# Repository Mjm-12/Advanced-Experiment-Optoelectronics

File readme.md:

# オシロスコープの使い方
このファイルは筑波大学理工学群、応用理工学類応用物理主専攻3年次の専攻実験(テーマ：オプトエレクトロニクス)用に作成しています。  
作成者は2025年度TAの山本隼大(関口・早田研、前期博士課程1年)です。  

使用するオシロスコープはKEYSIGHTの[**EDUX1052G**](https://www.keysight.com/jp/ja/product/EDUX1052G/oscilloscope-50-mhz-2-analog-channels-waveform-generator.html)です。  
マニュアルは[ここ](https://www.keysight.com/jp/ja/assets/9921-02770/user-manuals/9018-70020.pdf)からダウンロードできます。  
このオシロスコープは基本的な機能である波形の観察に加えて、ファンクションジェネレータ機能（波形を発生させる機能）や、周波数特性の測定を一台で完結することができる優れものです。  

他社製のオシロスコープでも同様の使い方で測定を行うことができるので、是非来年以降の研究でも参考にしていただければと思います。  

## プローブについて
プローブはオシロスコープと被測定物の電気的接続を取るためのものです。一般的には細長い棒状のものを使いますが、被測定物や測定する周波数帯によってはBNCケーブルなどを直接繋ぐこともあります。  

### プローブ倍率
プローブには倍率を切り替えるスイッチが付いています。一般的には1:1と10:1の2つが切り替え可能になっていることが多いですが、**本実験では10:1を基本として測定を行いましょう**。その理由としては、プローブの入力インピーダンスをできるだけ大きくして回路や信号への影響を最小限に留めるためです。  
オシロスコープの入力インピーダンスは1MΩ程度のものが多いですが、プローブを10:1にすることで、入力インピーダンスを10倍の10MΩにすることができます。その分、信号の電圧が1/10になってしまうので、オシロスコープ内部で10倍に増幅して表示することになります。  

#### オシロスコープ側の設定
まず、プローブの倍率を変更したいチャンネルを選択します。ここでは例として**Ch1**を選択します。  

**プローブの倍率の確認方法その1**  

次に画面右側のプローブを選択し、倍率をプローブと同様の値に変更します。  
この操作を怠ると、誤った電圧やゲインが表示されてしまうため、セットアップの一環として必ず確認するようにしましょう。  

**プローブの倍率の確認方法その2**  

### プローブの補正
オシロスコープのセットアップとして重要な設定に、プローブの補正があります。ケーブルやオシロスコープの入力部分には容量成分(コンデンサ成分)が存在するため、これを打ち消さないとプローブ自身がLRCフィルタとなってしまい、正しい測定ができません。  
そこで、直列にコンデンサ成分を追加して、容量成分を打ち消す必要があります。  
[参考資料](https://cc.cqpub.co.jp/system/contents/1246/)  

#### 補正方法
まず、補正したいプローブをオシロスコープ下部にある端子と図のように接続します。  

**プローブの接続方法**  

次に接続されているチャンネル選択ボタンを押して、ボタンが点灯していることを確認します。さらに、右上の`Auto Scale`ボタンを押すと、矩形波（方形波）が表示されるはずです。これで補正の準備完了です。  

**プローブ補正の手順**  

プローブには補正用のトリマーが付いています(図参照)。これを調整することで、直列のコンデンサ容量を調整します。エッジが適切な角度になり、理想的な矩形波が得られるように調整してください。十分に調整できたら問題ありません。  

**最適な形状に調整する**  

## 波形の観察方法
オシロスコープの最も基本的な機能である波形観察の方法について解説します。  

まず、大前提として横軸(x軸)方向が時間軸、縦軸(y軸)方向が電圧軸になります。サイン波を印加すれば $y=\sin{x}$ のグラフが描画されるイメージです。上部に時間や電圧のスケールが書いてありますが、これは1目盛りあたりの値を示しています。  

**時間軸と電圧軸で表される**  

### 軸の調整方法
ここからは実際に波形を見やすいい形に調整していきます。例として、プローブの補正に使う矩形波を使います。まず、補正時と同様に`Auto Scale`ボタンを押しましょう。そうすると、ある程度整った波形が描画されるはずです。  

**表示される波形の一例**  

次に、エッジ部分をもっと詳細に見たいとします。電圧軸を拡大・縮小するときは操作部中央の大きなツマミ(`Vertical`と書かれたツマミ)を調整します。ツマミを押し込むと、粗調整モードと微調整モードが切り替わります。  

電圧オフセット(中心の高さ)を切り替えたいときは下にある▲▼が書かれたツマミを調整します。押し込むことでオフセットがゼロに戻ります。  

時間軸方向の調整は`Horizontal`と書いてあるセクションで行います。左の大きいツマミが拡大縮小、右の小さいツマミが時間オフセットです。  
それぞれ押し込むことで、電圧軸方向のそれと同様の切り替えやオフセットのリセットが行えます。  

**電圧軸、時間軸の調整**  

### トリガーの設定
オシロスコープをマスターするうえで、最も重要な設定が**トリガー**です。トリガーとは時間で変動する電圧を安定的に表示するための機能です。トリガーを適切に設定しないと大きく荒ぶった波形となり、これでは到底測定には役立ちません。測定したい波形を確実に捉えるために必須となる機能であり、多くのモードがありますが、今回は低周波を扱ううえで最も基本的な設定に絞って紹介します。  

まず、トリガーモードはいくつかありますが、とりあえず最も一般的なトリガーである**エッジトリガー**を用いることにします。エッジトリガーにも立ち上がりを検出するものと立ち下がりを検出するものがありますが、一般的には立ち上がりを検出するものを選択するとよいでしょう。操作パネル右端の`Trigger`ボタンを押すとトリガーの設定画面が表示されるので、`Trigger Type`に**Edge**、`Slope`に上向きのダイオードのような図を選択します。  

**トリガーの調整**  

次に、トリガーのソースを設定します。これはトリガーをかける波形を選択するもので、今回は**Ch1**を選択します。内蔵のファンクションジェネレータを測定に使っている場合はWave Genをソースに選択してもよいでしょう。  

最後に、トリガーレベルを調整します。右端の`Trigger`と書かれたツマミを調整することで、オレンジのバーが上下することが確認できます。このオレンジバーの横線をトリガーレベルといい、この電圧を超える波形のみを取り出し、表示することができます。  
正しくトリガーを設定すると、波形が安定して表示されます。  

### 各数値を調べる
表示している波形の電圧や周波数を確認したいタイミングは往々にしてありますが、毎度目盛りを読むのは面倒なものです。そのため、デジタルオシロスコープには周波数や周期、電圧の振幅のピーク値や実効値を表示してくれる機能があります。  
`Meas`ボタンを押すことでサイドバーにMeasurementモードが開きます。そこから`Source`を選択し、`Type`を選択します。セレクトノブを押し込むか、`Add Measurement`を押すことで、下部に固定表示することができます。測定データは最大5個まで追加できます。  

**波形の特性の測定方法**  

**複数のSourceの特性を同時に見ることができる**  

### 波形表示を一時停止する
波形表示を一時停止するには右上の`RUN/STOP`ボタンを押します。すると波形が止まり、ボタンが赤くなると思います。  
再開するにはもう一度`RUN/STOP`ボタンを押せばOKです。  

## 周波数特性分析(FRA)
**FRA**(Frequency Response Analyzer)は装置の周波数応答を調べる装置を指し、この機能が本実験で用いるオシロスコープでは実装されています。アンプ等の周波数特性を分析することで、増幅可能な周波数レンジを定量的に評価することが可能です。理想的な特性としては低周波まで高周波まで真っ直ぐ伸びていることが望ましいです。例えば、あるヘッドホンアンプの周波数特性が人間の可聴域より狭いと、音が籠もって聞こえたり、キンキンして聞こえることがあります。また、低周波だけ強い特性を持つ場合は、ベースやバスドラムなどの低音が強調されて聞こえます。  

### 基本的なセットアップ
まず、`Analyze`→`Features`を開き、FRAを選択します。そうすると、左側にグラフが表示されます。  

**FRAのセットアップ方法①**  

次に、被測定物にプローブを取り付けていきます。Setupを開くと、ディレクションが表示されるので、このように接続していきます。具体的にはGenOutと**Ch1**を入力、Ch2を出力に取り付けます。  

**FRAセットアップ方法②(Setupを押すと表示される画面)**  

FRA Setupの画面に戻り、測定のためのパラメータを調整していきます。`Start Freq`と`Stop Freq`に測定したい周波数の上限/下限を入力します。例として、可聴帯域を測定したいとするならば**10Hz~20kHz程度**が望ましいでしょう。  
`Amplitude`は入力するサイン波の大きさを調整します。クリップ（音割れ）しない範囲で調整しつつ、小さすぎるとノイズの影響が支配的になってしまい、正確な測定ができません。あらかじめどれくらいの大きさの信号ならクリップしないか確認しておきましょう。  
`Output Load`はとりあえず**50Ω**で構いません。`Points`は測定点数を示し、点数が多いほど精密な測定が期待出来ますが、その分測定時間が長くなります。可聴域程度であれば**200~300程度**でも十分だと思います。  

### 結果の見方
`ゲイン(Gain)`が<span style="color:#157EFB;">青線</span>、`位相(Phase)`が<span style="color:red;">赤線</span>で表示されています。x軸は周波数で、ゲインの単位はdBで、 $A\,\mathrm{[dB]}=20\log_{10}\frac{V_{OUT}}{V_{IN}}$ で表される無次元量です。0dBで1倍、3dBで約√2倍、6dBで約2倍、20dBで10倍、40dBで100倍と覚えてください。位相は基準信号からの位相のズレを表していますが、本実験ではあまり重要ではないので無視して構いません。回路の発振可能性を評価するときなどに用いられます。  

**FRA結果の一例 [被測定物：家に転がっていたエレキギター用のエフェクター(自作)]**  

### 結果の保存方法
『*データの保存方法*』>『*FRA結果を保存する*』項を参照。  

## 高速フーリエ変換(FFT)
高速フーリエ変換とは離散フーリエ変換を計算機上で高速に計算するアルゴリズムです(Wikipedia)。測定した波形を周波数成分に分解することができます。  

### 基本的なセットアップ
FFTを呼び出す方法は簡単です。下側にある`FFT`ボタンを押すだけです。  

そうするとFFTの設定画面が表示されます。`Span`は表示する周波数帯の広さを、`Center`は画面中央に位置する周波数を設定することができます。  

ただし、歪み率の計算などの細かい分析はできません。詳細な分析が必要な場合は後述の『*Pythonを使ってFFTする*』項を参照してください。  

**FFT結果の表示例**、このように時間範囲を広げるとFFTの周波数分解能が向上する  

### 高分解能化のテクニック
FFTの周波数分解能（どれくらい細かく周波数を分けて分析できるかという指標）は、基本的に解析時間 $T$ の逆数 $\frac{1}{T}$ に依存します。多くのオシロスコープでは、FFTに用いるデータが画面表示範囲と連動しているため、高い分解能を得るには、図のように時間幅を広く取ることが必要になります。  

しかし、**サンプル数**（FFTで解析するデータ点の数）はオシロスコープごとに固定されている場合が多く（たとえば、EDUX1052Gの場合は最大50,000点）であり、時間幅を広げすぎると1秒間あたりのサンプル数を示す**サンプリング周波数** $f_s\,[\mathrm{Hz}]$ が低下してしまいます。サンプリング周波数が下がると、FFTで表示可能な最大周波数である**ナイキスト周波数** $f_N\,[\mathrm{Hz}]$（ $f_N = \frac{f_s}{2}$ ）も下がってしまい、高周波数帯域が十分に解析できなくなる可能性があります。  
例えば上の図のように1グリッドあたり20msのとき、画面全体に表示されている時間幅は200msなので、サンプリング周波数 $f_s=\frac{50,000}{200\,\mathrm{[ms]}}=250\,\mathrm{kHz}$ となり、ナイキスト周波数 $f_N$ はこの半分の $125\,\mathrm{kHz}$ となります。  

まとめると、時間幅を大きくすると周波数分解能は上がりますが、過度に時間幅を広くしすぎるとサンプリング周波数が下がり、最大解析周波数が低くなってしまいます。逆に、時間幅を小さくしすぎると周波数分解能が粗くなるため、高すぎる周波数しか解析できなくなる可能性があります。オシロスコープでFFTを行う際は、**時間幅、サンプリング周波数**のバランスを考えながら、解析したい周波数帯域と分解能の両方を満たす設定を見つけることが大切です。  

参考までに、もし時間窓が短い場合、分解能が低下し下画像の様にピークの裾引きが長くなります。  

**波形の表示範囲が狭いと周波数分解能が低下する**  

### Pythonを使ってFFTする
波形のFFT結果を知るために最も簡単で合理的な方法はPythonを使う方法でしょう。私はコーディングのスキルがまったくないので、ChatGPTとやりとりして書いてもらいました。使用モデルはo3-mini-highです。  
Google Colabを利用して実行する方法とローカル環境で実行する方法の二つを用意しました。  

Google Colabを用いる方法は[こちら](https://github.com/Mjm-12/Advanced-Experiment-Optoelectronics/edit/main/Appendix_A)から。  

ローカル環境で実行したい場合は[こちら](https://github.com/Mjm-12/Advanced-Experiment-Optoelectronics/edit/main/Python_FFT)からスクリプトをダウンロードして利用してください。  

## データの保存方法
結果の解析や実験レポートのために結果を保存したい場合は多々あります。勿論波形の観察のみではなく、記録も可能な機種がほとんどですから、是非活用してより深い考察をしてほしいです。  

### 波形データを保存する
オシロスコープ側の操作をする前に、まずUSBメモリを前面のUSBポートに差し込みます。  

次に、Save/Recallボタンを押します。すると下のような画面が表示されるのでFormatからCSVを選択します。  

**波形データをCSVで保存する方法**  

`Save to`で保存するディレクトリを選択できます。デフォルトではUSBメモリが選択されていると思いますから、そのままでも問題なく利用できます。  
また、`File Name`からお好みの名前を設定できます。  

`Settings`では記録するサンプル数を変更できます。記録した波形を基にFFTをしようと考えている場合は最大の50,000にするとナイキスト周波数を伸ばすことができ、幅広い周波数帯でFFTすることができます（時間範囲を広げるのを忘れずに）。  

最後に`Press to Save`を押すと、USBメモリに結果が保存されます。サンプル数が多いとその分保存に時間がかかります。  

また、オシロスコープ側のFFTが有効な状態で波形を記録すると、CSVファイル内に波形データに続いて、FFT結果も記録されます。  

次回から同様の設定で波形データを保存したい場合、操作パネル右側にある`Save to USB`を選択することで一発で保存できるため便利です。  

**Save to USBを押すことで同様の設定で保存できる**  

### FRA結果を保存する
まず、波形の保存と同様にUSBメモリを差し込み、それから`Format`からFRA dataを選択します（下図参照）。  

**FRA結果を保存する方法**

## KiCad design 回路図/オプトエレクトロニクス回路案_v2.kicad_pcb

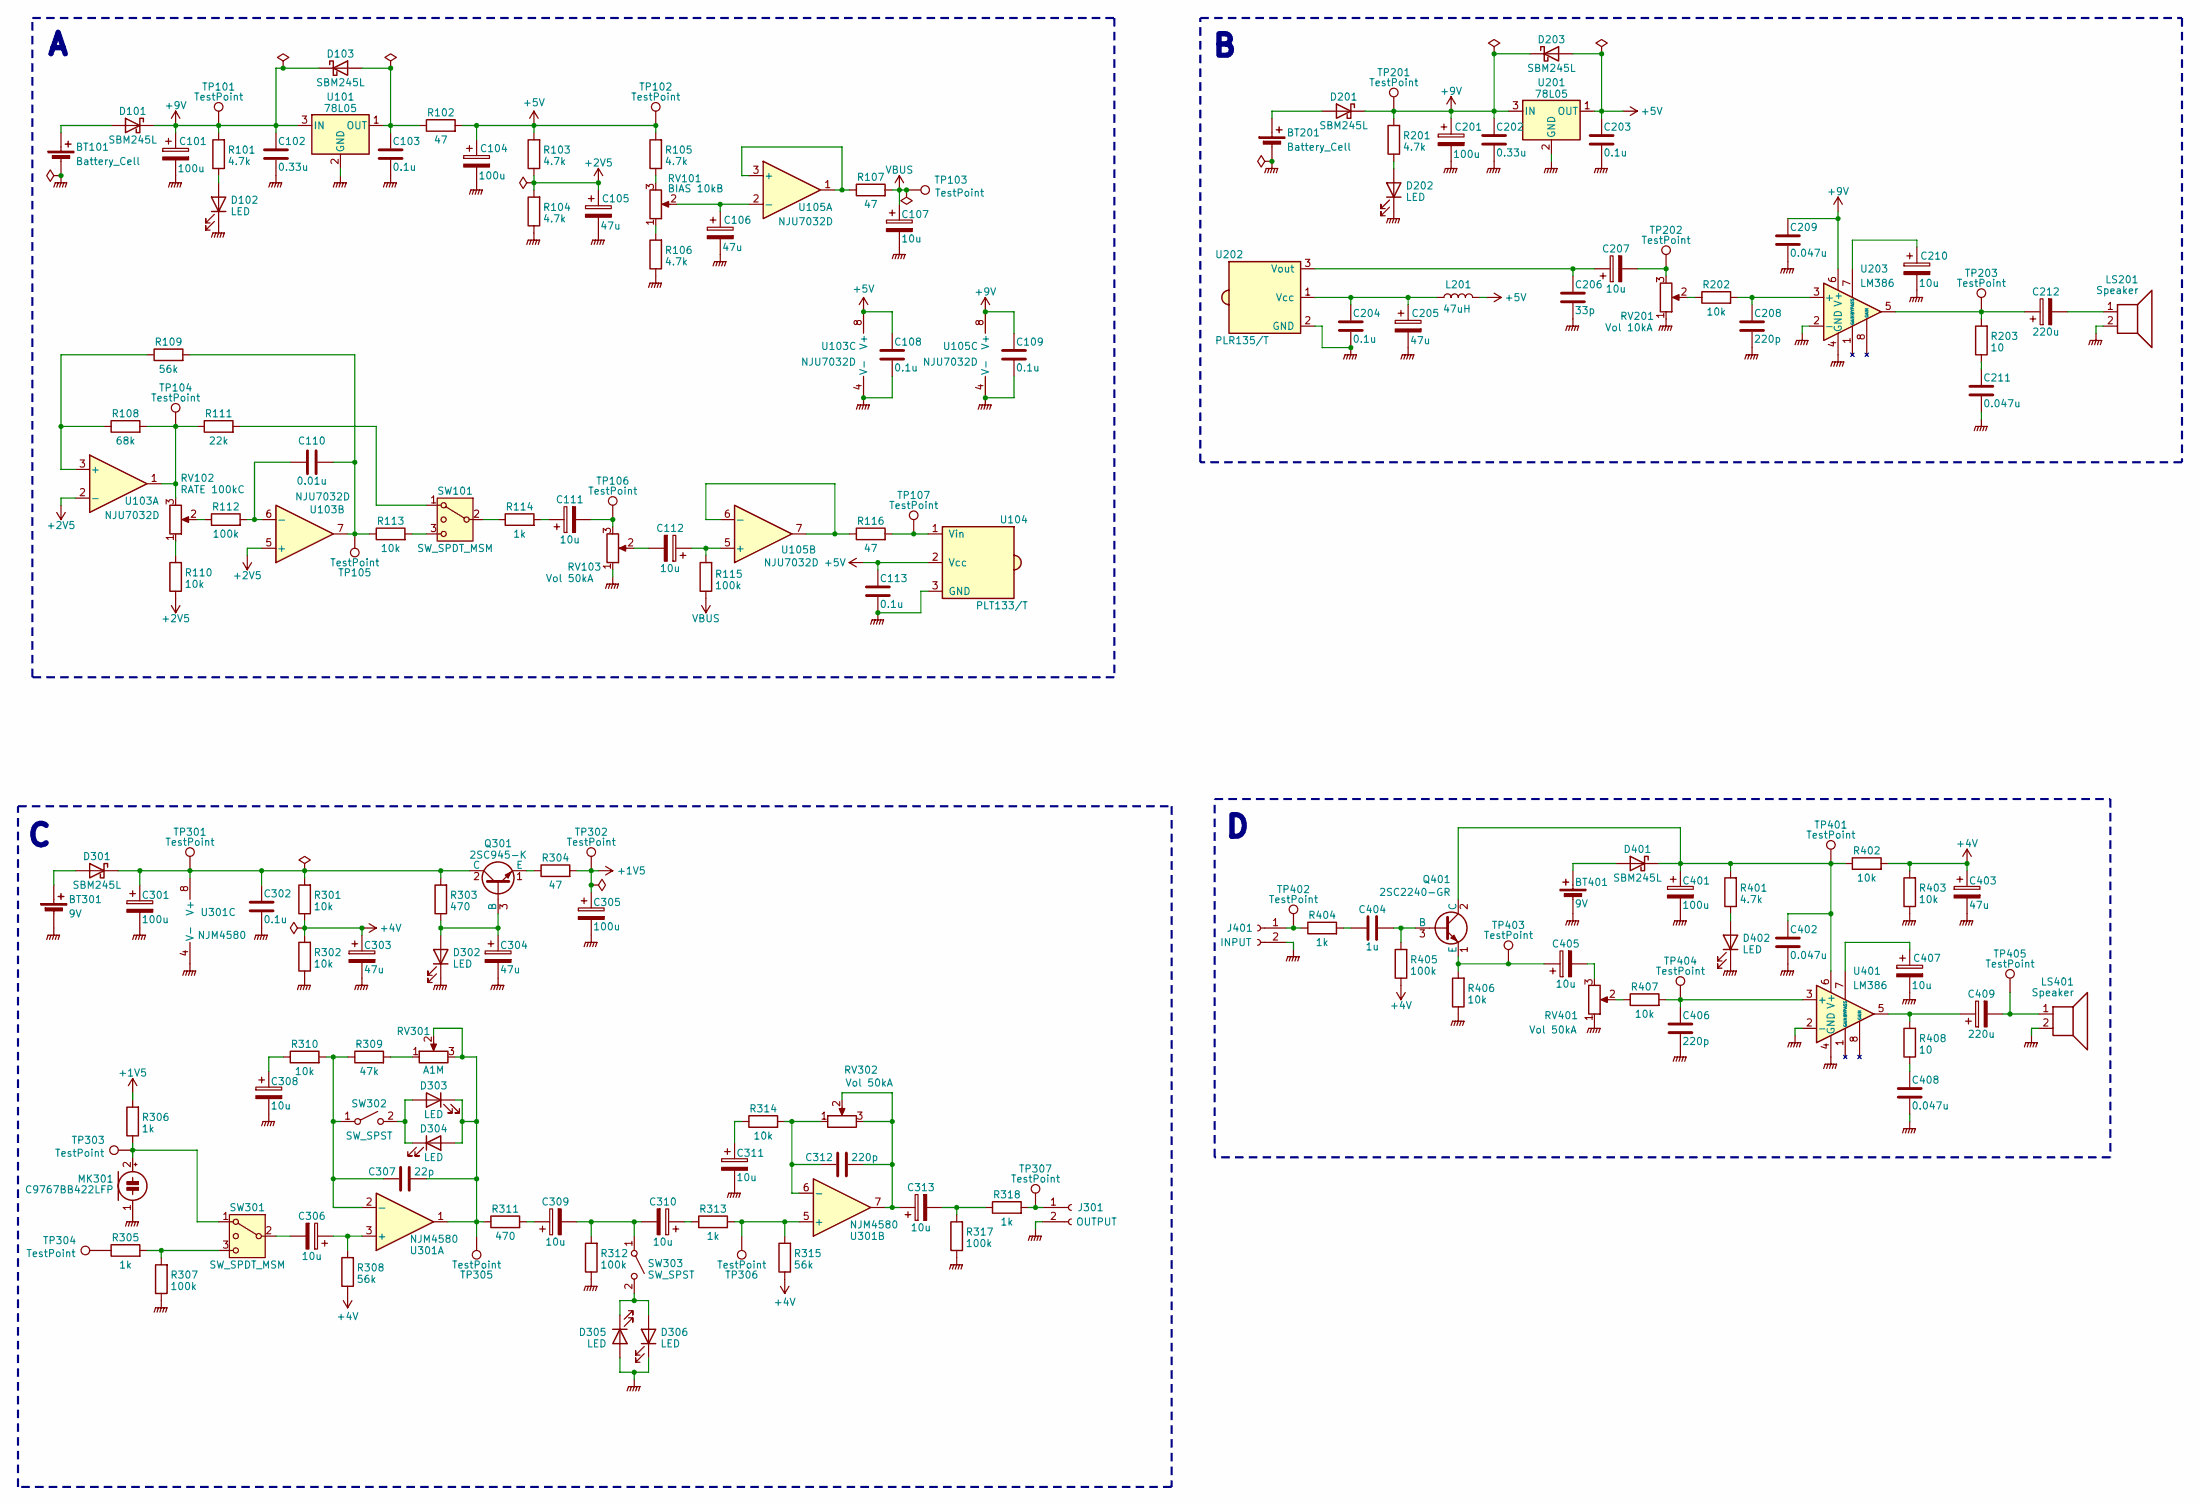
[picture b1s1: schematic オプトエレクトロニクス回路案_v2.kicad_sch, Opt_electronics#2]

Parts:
BT101, BT201: Battery_Cell; PanelMount_2pin
BT301, BT401: 9V; PanelMount_2pin
C101, C104, C201: 100u; CP_Radial_D6.3mm_P2.50mm
C102, C202: 0.33u; C_Disc_D4.3mm_W1.9mm_P5.00mm; LCSC C1623
C103, C108, C109, C113, C203, C204, C302: 0.1u; C_Disc_D4.3mm_W1.9mm_P5.00mm; LCSC C49678
C105, C106, C205: 47u; CP_Radial_D6.3mm_P2.50mm
C107, C111, C112, C207, C210, C306, C308, C309, C310, C311, C313, C405, C407: 10u; CP_Radial_D4.0mm_P1.50mm
C110: 0.01u; C_Disc_D7.5mm_W2.5mm_P5.00mm
C206: 33p; C_Disc_D4.3mm_W1.9mm_P5.00mm; LCSC C49678
C208, C406: 220p; C_Disc_D4.3mm_W1.9mm_P5.00mm; LCSC C49678
C209, C211, C402, C408: 0.047u; C_0805_2012Metric; LCSC C49678
C212, C409: 220u; CP_Radial_D8.0mm_P3.50mm; LCSC C7171
C301, C305, C401: 100u; CP_Radial_D6.3mm_P2.50mm; LCSC C7171
C303, C304, C403: 47u; CP_Radial_D6.3mm_P2.50mm; LCSC C7171
C307: 22p; C_Disc_D4.3mm_W1.9mm_P5.00mm
C312: 220p; C_Disc_D4.3mm_W1.9mm_P5.00mm
C404: 1u; C_Disc_D7.5mm_W6.0mm_P5.00mm(For Film 1uF)
D101, D103, D201, D203, D301, D401: SBM245L; D_DO-41_SOD81_P7.62mm_Horizontal; LCSC C191023
D102, D202, D302, D303, D304, D305, D306, D402: LED; LED_D3.0mm
J301: OUTPUT; JST_XH_B2B-XH-A_1x02_P2.50mm_Vertical
J401: INPUT; JST_XH_B2B-XH-A_1x02_P2.50mm_Vertical
L201: 47uH; L_Axial_L7.0mm_D3.3mm_P10.16mm_Horizontal_Fastron_MICC
LS201, LS401: Speaker; Speaker_50mm
MK301: C9767BB422LFP
Q301: 2SC945-K; TO-92_Inline_Wide
Q401: 2SC2240-GR; TO-92_Inline_Wide
R101, R103, R104, R105, R106, R201, R401: 4.7k; R_Axial_DIN0207_L6.3mm_D2.5mm_P7.62mm_Horizontal
R102, R107, R116, R304: 47; R_Axial_DIN0207_L6.3mm_D2.5mm_P7.62mm_Horizontal
R108: 68k; R_Axial_DIN0207_L6.3mm_D2.5mm_P7.62mm_Horizontal
R109, R308, R315: 56k; R_Axial_DIN0207_L6.3mm_D2.5mm_P7.62mm_Horizontal
R110, R113, R202, R301, R302, R310, R314, R402, R403, R406, R407: 10k; R_Axial_DIN0207_L6.3mm_D2.5mm_P7.62mm_Horizontal
R111: 22k; R_Axial_DIN0207_L6.3mm_D2.5mm_P7.62mm_Horizontal
R112, R115, R307, R312, R317, R405: 100k; R_Axial_DIN0207_L6.3mm_D2.5mm_P7.62mm_Horizontal
R114, R305, R306, R313, R318, R404: 1k; R_Axial_DIN0207_L6.3mm_D2.5mm_P7.62mm_Horizontal
R203, R408: 10; R_Axial_DIN0207_L6.3mm_D2.5mm_P7.62mm_Horizontal
R303, R311: 470; R_Axial_DIN0207_L6.3mm_D2.5mm_P7.62mm_Horizontal
R309: 47k; R_Axial_DIN0207_L6.3mm_D2.5mm_P7.62mm_Horizontal
RV101: BIAS 10kB; TCOS_GF063P
RV102: RATE 100kC; TCOS_GF063P
RV103, RV302, RV401: Vol 50kA; TCOS_GF063P
RV201: Vol 10kA; TCOS_GF063P
RV301: A1M; TCOS_GF063P
SW101, SW301: SW_SPDT_MSM; Toggle_SW_mini_2MS1-T1-B4-M2-Q-E
SW302, SW303: SW_SPST; Toggle_SW_mini_2MS1-T1-B4-M2-Q-E
TP101, TP102, TP103, TP104, TP105, TP106, TP107, TP201, TP202, TP203, TP301, TP302, TP303, TP304, TP305, TP306, TP307, TP401, TP402, TP403, TP404, TP405: TestPoint; PanelMount_Jack
U101, U201: 78L05; TO-92_Inline_Wide
U103, U105: NJU7032D; DIP-8_W7.62mm
U104: PLT133/T; PLT133T
U202: PLR135/T; PLR135T
U203, U401: LM386; DIP-8_W7.62mm
U301: NJM4580; DIP-8_W7.62mm

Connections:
+1V5: C305.1, R304.2, R306.2, TP302.1
+2V5: C105.1, R103.1, R104.2, R110.1, U103.2 (-), U103.5 (+)
+4V: C303.1, C403.1, R301.1, R302.2, R308.1, R315.1, R402.2, R403.2, R405.1
+5V: C104.1, C108.1, C113.1, C203.1, D203.2 (A), L201.2, R102.2, R103.2, R105.2, TP102.1, U103.8 (V+), U104.2 (Vcc), U201.1 (OUT)
+9V: C101.1, C102.1, C109.1, C201.1, C202.1, C209.1, D101.1 (K), D103.1 (K), D201.1 (K), D203.1 (K), R101.2, R201.2, TP101.1, TP201.1, U101.3 (IN), U105.8 (V+), U201.3 (IN), U203.6 (V+)
GNDPWR: BT101.2 (-), BT201.2 (-), BT301.2 (-), BT401.2 (-), C101.2, C102.2, C103.2, C104.2, C105.2, C106.2, C107.2, C108.2, C109.2, C113.2, C201.2, C202.2, C203.2, C204.2, C205.2, C206.2, C208.2, C209.2, C210.2, C211.2, C301.2, C302.2, C303.2, C304.2, C305.2, C308.2, C311.2, C401.2, C402.2, C403.2, C406.2, C407.2, C408.2, D102.1 (K), D202.1 (K), D302.1 (K), D305.2 (A), D306.1 (K), D402.1 (K), J301.2, J401.2, LS201.2, LS401.2, MK301.1 (-), R104.1, R106.1, R302.1, R307.1, R312.1, R317.1, R403.1, R406.1, RV103.1, RV201.1, RV401.1, U101.2 (GND), U103.4 (V-), U104.3 (GND), U105.4 (V-), U201.2 (GND), U202.2 (GND), U203.2 (-), U203.4 (GND), U301.4 (V-), U401.2 (-), U401.4 (GND)
unnamed: BT101.1 (+), D101.2 (A)
unnamed: BT201.1 (+), D201.2 (A)
unnamed: BT301.1 (+), D301.2 (A)
unnamed: BT401.1 (+), D401.2 (A)
unnamed: C110.2, R109.2, R113.1, TP105.1, U103.7
unnamed: C111.1, R114.2
unnamed: C111.2, RV103.3, TP106.1
unnamed: C112.2, RV103.2
unnamed: C207.2, RV201.3, TP202.1
unnamed: C211.1, R203.1
unnamed: C212.1, R203.2, TP203.1, U203.5
unnamed: C212.2, LS201.1
unnamed: C308.1, R310.1
unnamed: C309.1, R311.2
unnamed: C310.1, R313.1
unnamed: C311.1, R314.1
unnamed: C312.2, C313.1, RV302.2, RV302.3, U301.7
unnamed: C313.2, R317.2, R318.1
unnamed: C404.1, R404.2
unnamed: C405.2, RV401.3
unnamed: C408.1, R408.1
unnamed: C409.1, R408.2, U401.5
unnamed: C409.2, LS401.1, TP405.1
unnamed: D102.2 (A), R101.1
unnamed: C103.1, D103.2 (A), R102.1, U101.1 (OUT)
unnamed: D202.2 (A), R201.1
unnamed: C301.1, C302.1, D301.1 (K), Q301.2 (C), R301.2, R303.2, TP301.1, U301.8 (V+)
unnamed: C304.1, D302.2 (A), Q301.3 (B), R303.1
unnamed: D303.2 (A), D304.1 (K), SW302.2 (B)
unnamed: C307.2, D303.1 (K), D304.2 (A), R311.1, RV301.2, RV301.3, TP305.1, U301.1
unnamed: D305.1 (K), D306.2 (A), SW303.2 (B)
unnamed: C401.1, C402.1, D401.1 (K), Q401.2 (C), R401.2, R402.1, TP401.1, U401.6 (V+)
unnamed: D402.2 (A), R401.1
unnamed: J301.1, R318.2, TP307.1
unnamed: J401.1, R404.1, TP402.1
unnamed: MK301.2 (+), R306.1, SW301.1, TP303.1
unnamed: Q301.1 (E), R304.1
unnamed: C404.2, Q401.3 (B), R405.2
unnamed: C405.1, Q401.1 (E), R406.2, TP403.1
unnamed: R105.1, RV101.3
unnamed: R106.2, RV101.1
unnamed: R108.2, R111.1, RV102.3, TP104.1, U103.1
unnamed: R110.2, RV102.1
unnamed: R111.2, SW101.1
unnamed: R112.1, RV102.2
unnamed: R202.1, RV201.2
unnamed: R305.1, TP304.1
unnamed: R309.2, RV301.1
unnamed: R407.1, RV401.2
unnamed: R114.1, SW101.2 (3)
unnamed: R113.2, SW101.3 (4)
unnamed: C306.2, SW301.2 (3)
unnamed: R305.2, R307.2, SW301.3 (4)
unnamed: C307.1, R309.1, R310.2, SW302.1 (A), U301.2 (-)
unnamed: C309.2, C310.2, R312.2, SW303.1 (A)
unnamed: R108.1, R109.1, U103.3 (+)
unnamed: C110.1, R112.2, U103.6 (-)
unnamed: R116.2, TP107.1, U104.1 (Vin)
unnamed: R107.1, U105.1, U105.3 (+)
unnamed: C106.1, RV101.2, U105.2 (-)
unnamed: C112.1, R115.2, U105.5 (+)
unnamed: R116.1, U105.6 (-), U105.7
unnamed: C204.1, C205.1, L201.1, U202.1 (Vcc)
unnamed: C206.1, C207.1, U202.3 (Vout)
unnamed: C208.1, R202.2, U203.3 (+)
unnamed: C210.1, U203.7 (BYPASS)
unnamed: C306.1, R308.2, U301.3 (+)
unnamed: R313.2, R315.2, TP306.1, U301.5 (+)
unnamed: C312.1, R314.2, RV302.1, U301.6 (-)
unnamed: C406.1, R407.2, TP404.1, U401.3 (+)
unnamed: C407.1, U401.7 (BYPASS)
VBUS: C107.1, R107.2, R115.1, TP103.1

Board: 2 copper layers, 159 parts (0 on the bottom side), 78 nets, no tracks yet.

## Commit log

2025-02-21 ファイル類を追加
2025-02-21 画像をフォルダへ移動
2025-04-08 ファイルの更新
2025-04-08 相対パスを修正
2025-04-08 リンクを修正
2025-04-08 リンクの修正2
2025-04-08 数式の修正
2025-04-08 ファイルの分割(appendix)
2025-04-08 軽微な修正
2025-04-08 ファイルパスの修正
2025-04-13 Add schematics
2025-04-20 add layout
2025-05-20 no message
2025-05-20 Added contact information
2025-05-27 Added reference material
2025-10-03 回路Aの修正
2025-10-09 移行のため
2025-10-09 spiceモデルの追加
2025-10-10 パラメータ修正
2026-01-20 change checklist
2026-01-27 add md
